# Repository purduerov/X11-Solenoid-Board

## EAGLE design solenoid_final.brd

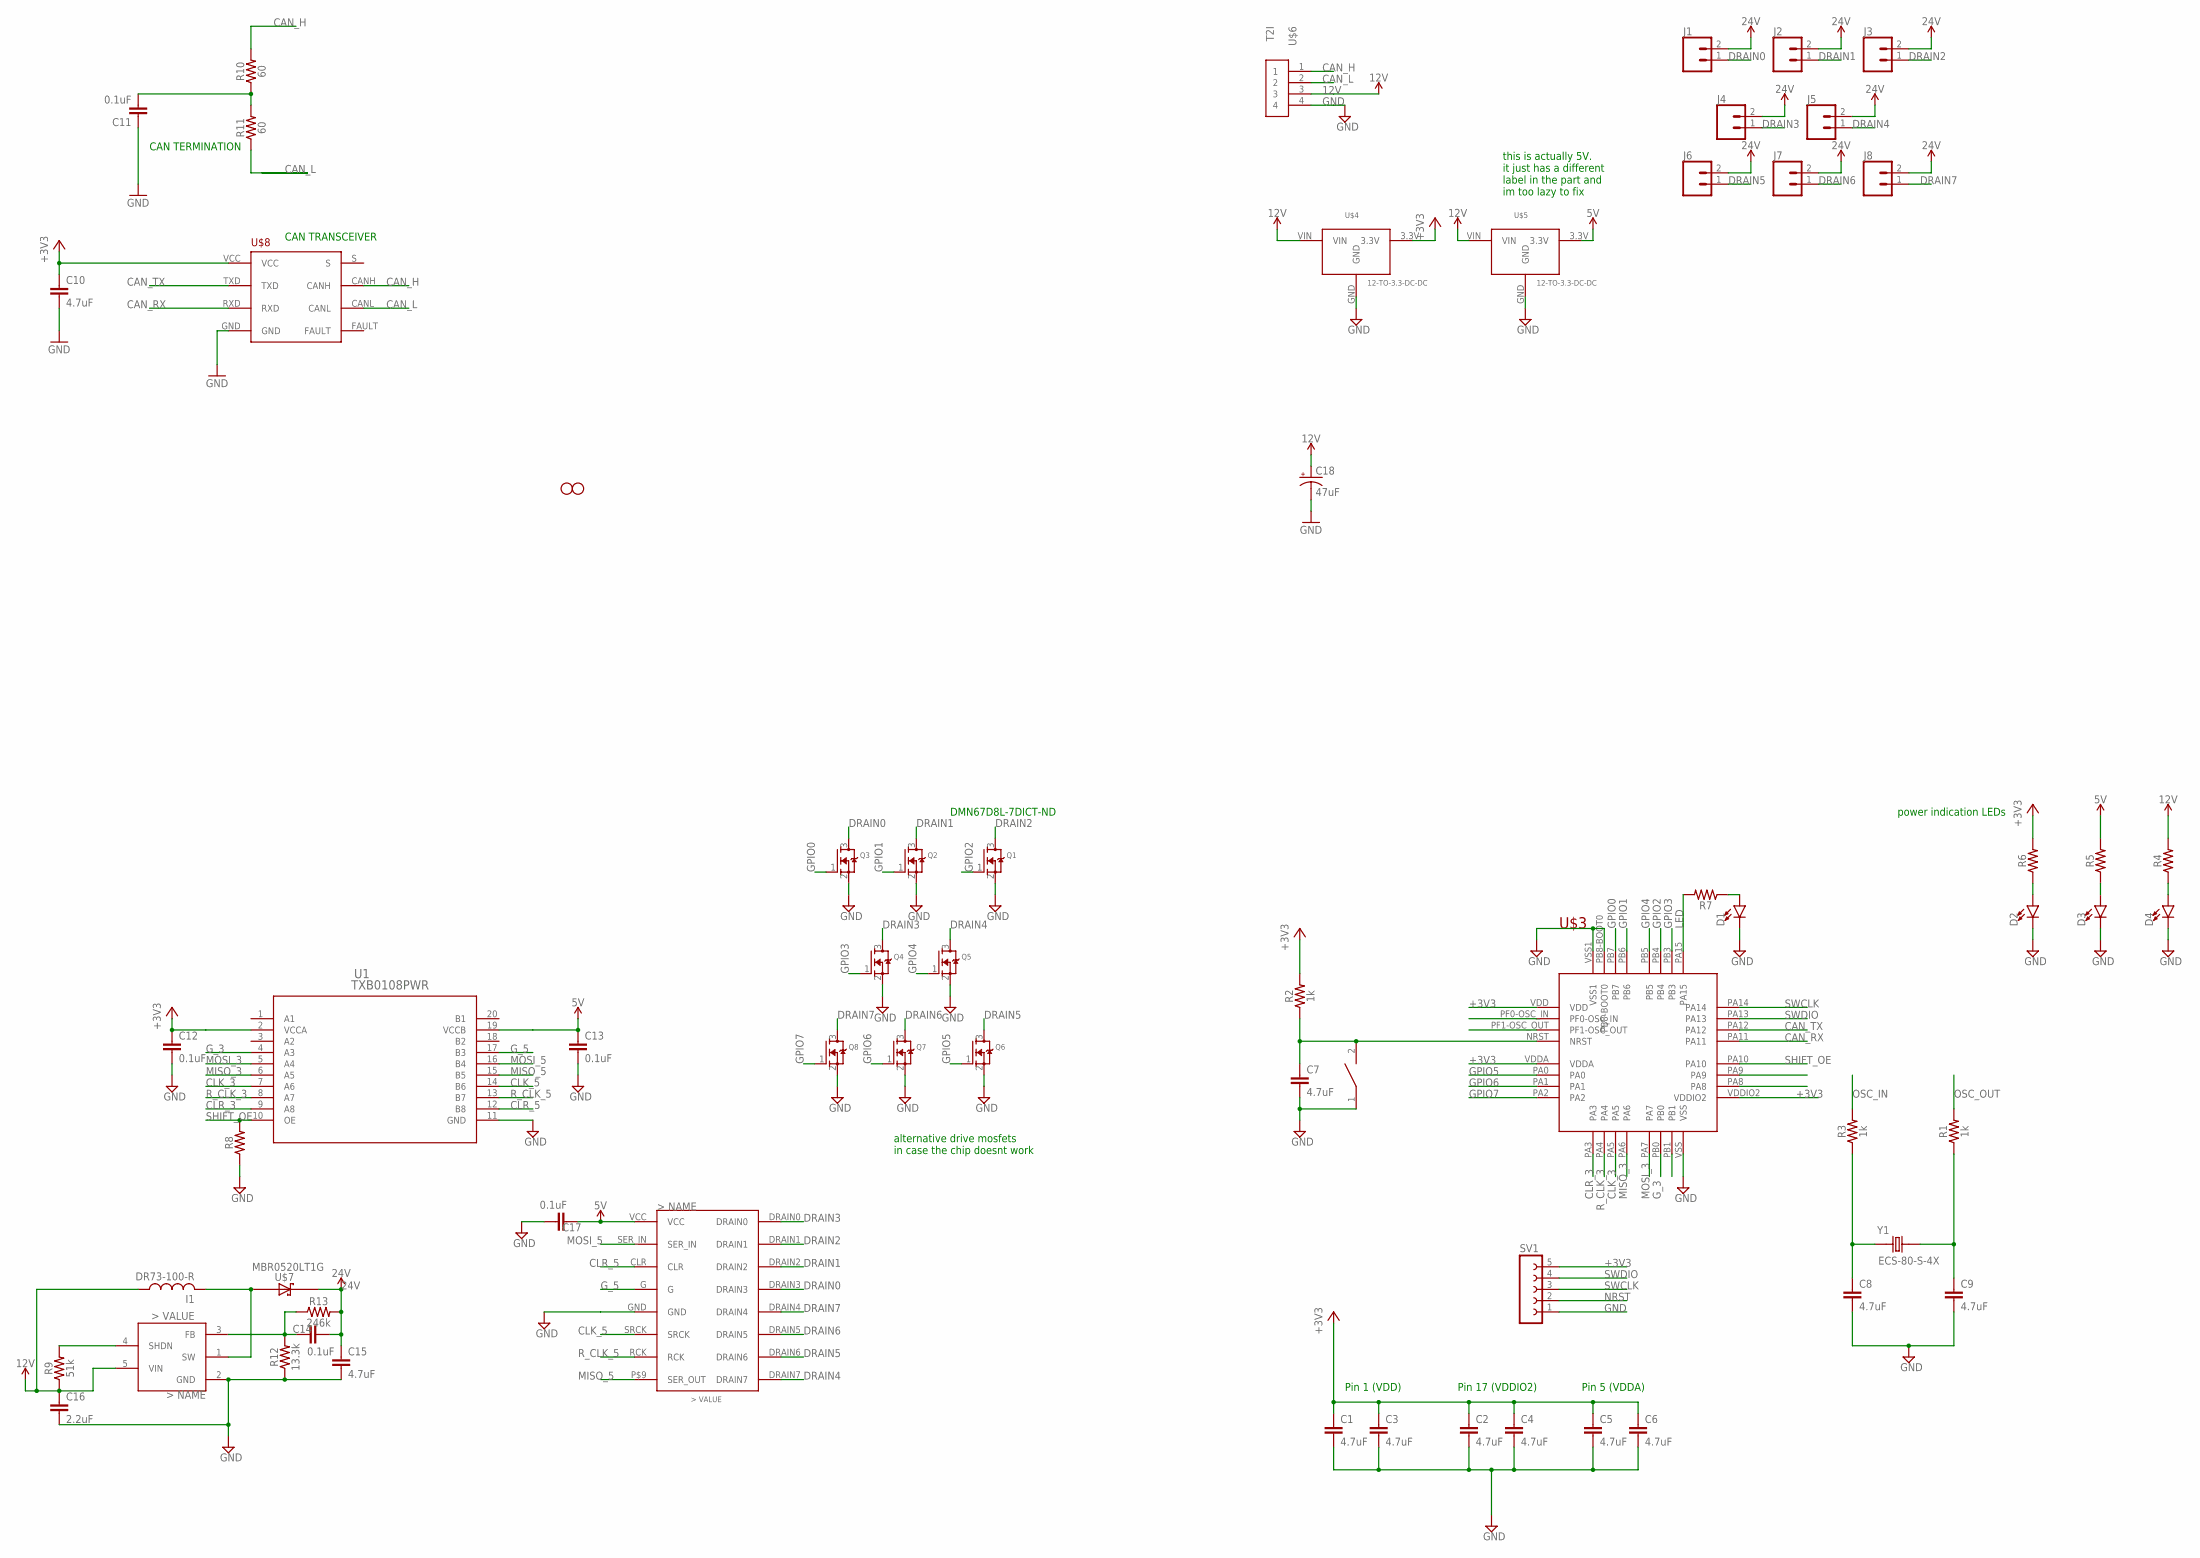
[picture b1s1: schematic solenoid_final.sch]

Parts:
C1, C2, C3, C4, C5, C6, C7, C8, C9, C10, C15: 4.7uF; 0603
C11, C12, C13, C14, C17: 0.1uF; 0603
C16: 2.2uF; 0603
C18: 47uF; PANASONIC_D
D1, D2, D3, D4: LED0603; LED-0603
H1, H2: STAND-OFF
I1: DR73-100-R
J1, J2, J3, J4, J5, J6, J7, J8: CONN_02; 1X02
Q1, Q2, Q3, Q4, Q5, Q6, Q7, Q8: MOSFET-NWIDE; SOT23-WIDE
R1, R2, R3: 1k; 0603
R4, R5, R6, R7, R8: 0603
R9: 51k; 0603
R10, R11: 60; 0603
R12: 13.3k; 0603
R13: 246k; 0603
RESET: SWITCH; SW_2512
SV1: FE05-1
U1: TXB0108PWR; PW20
U$1: SHIFT_REGISTER
U$2: LM27313; SOT95P300X145-5
U$3: STM32F042K6T6
U$4, U$5: 12-TO-3.3-DC-DC; MURATA-DCDC
U$6: T2I
U$7: MBR0520LT1G; SOD3716X135
U$8: TCAN337D
Y1: ECS-80-S-4X; XTAL_ECS-80-S-4X

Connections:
5V: C13.1, C17.1, R5.2, U1.19 (VCCB), U$1.VCC, U$5.3.3V
12V: C16.1, C18.+, I1.1, R4.2, R9.1, U$2.5 (VIN), U$4.VIN, U$5.VIN, U$6.3
24V: C14.2, C15.1, J1.2, J2.2, J3.2, J4.2, J5.2, J6.2, J7.2, J8.2, R13.2, U$7.2 (C)
+3V3: C1.1, C2.1, C3.1, C4.1, C5.1, C6.1, C10.1, C12.1, R2.2, R6.2, SV1.5, U1.2 (VCCA), U$3.VDD, U$3.VDDA, U$3.VDDIO2, U$4.3.3V, U$8.VCC
CAN_H: R10.2, U$6.1, U$8.CANH
CAN_L: R11.1, U$6.2, U$8.CANL
CAN_RX: U$3.PA11, U$8.RXD
CAN_TX: U$3.PA12, U$8.TXD
CLK_3: U1.7 (A6), U$3.PA5
CLK_5: U1.14 (B6), U$1.SRCK
CLR_3: U1.9 (A8), U$3.PA3
CLR_5: U1.12 (B8), U$1.CLR
DRAIN0: J1.1, Q3.3 (D), U$1.DRAIN3
DRAIN1: J2.1, Q2.3 (D), U$1.DRAIN2
DRAIN2: J3.1, Q1.3 (D), U$1.DRAIN1
DRAIN3: J4.1, Q4.3 (D), U$1.DRAIN0
DRAIN4: J5.1, Q5.3 (D), U$1.DRAIN7
DRAIN5: J6.1, Q6.3 (D), U$1.DRAIN6
DRAIN6: J7.1, Q7.3 (D), U$1.DRAIN5
DRAIN7: J8.1, Q8.3 (D), U$1.DRAIN4
GND: C1.2, C2.2, C3.2, C4.2, C5.2, C6.2, C7.2, C8.2, C9.2, C10.2, C11.1, C12.2, C13.2, C15.2, C16.2, C17.2, C18.-, D1.C, D2.C, D3.C, D4.C, Q1.2 (S), Q2.2 (S), Q3.2 (S), Q4.2 (S), Q5.2 (S), Q6.2 (S), Q7.2 (S), Q8.2 (S), R8.1, R12.1, RESET.1, SV1.1, U1.11 (GND), U$1.GND, U$2.2 (GND), U$3.PB8-BOOT0, U$3.VSS, U$3.VSS1, U$4.GND, U$5.GND, U$6.4, U$8.GND
GPIO0: Q3.1 (G), U$3.PB7
GPIO1: Q2.1 (G), U$3.PB6
GPIO2: Q1.1 (G), U$3.PB4
GPIO3: Q4.1 (G), U$3.PB3
GPIO4: Q5.1 (G), U$3.PB5
GPIO5: Q6.1 (G), U$3.PA0
GPIO6: Q7.1 (G), U$3.PA1
GPIO7: Q8.1 (G), U$3.PA2
G_3: U1.4 (A3), U$3.PB0
G_5: U1.17 (B3), U$1.G
LED: R7.2, U$3.PA15
MISO_3: U1.6 (A5), U$3.PA6
MISO_5: U1.15 (B5), U$1.P$9 (SER_OUT)
MOSI_3: U1.5 (A4), U$3.PA7
MOSI_5: U1.16 (B4), U$1.SER_IN
unnamed: C9.1, R1.1, Y1.2
unnamed: C8.1, R3.1, Y1.1
unnamed: R9.2, U$2.4 (SHDN)
unnamed: C11.2, R10.1, R11.2
unnamed: I1.2, U$2.1 (SW), U$7.1 (A)
unnamed: C14.1, R12.2, R13.1, U$2.3 (FB)
unnamed: D1.A, R7.1
unnamed: D4.A, R4.1
unnamed: D3.A, R5.1
unnamed: D2.A, R6.1
NRST: C7.1, R2.1, RESET.2, SV1.2, U$3.NRST
OSC_IN: R3.2, U$3.PF0-OSC_IN
OSC_OUT: R1.2, U$3.PF1-OSC_OUT
R_CLK_3: U1.8 (A7), U$3.PA4
R_CLK_5: U1.13 (B7), U$1.RCK
SHIFT_OE: R8.2, U1.10 (OE), U$3.PA10
SWCLK: SV1.3, U$3.PA14
SWDIO: SV1.4, U$3.PA13

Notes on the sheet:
Pin 1 (VDD)
Pin 17 (VDDIO2)
Pin 5 (VDDA)
CAN TRANSCEIVER
CAN TERMINATION
this is actually 5V. it just has a different label in the part and im too lazy to fix
DMN67D8L-7DICT-ND
power indication LEDs
alternative drive mosfets in case the chip doesnt work

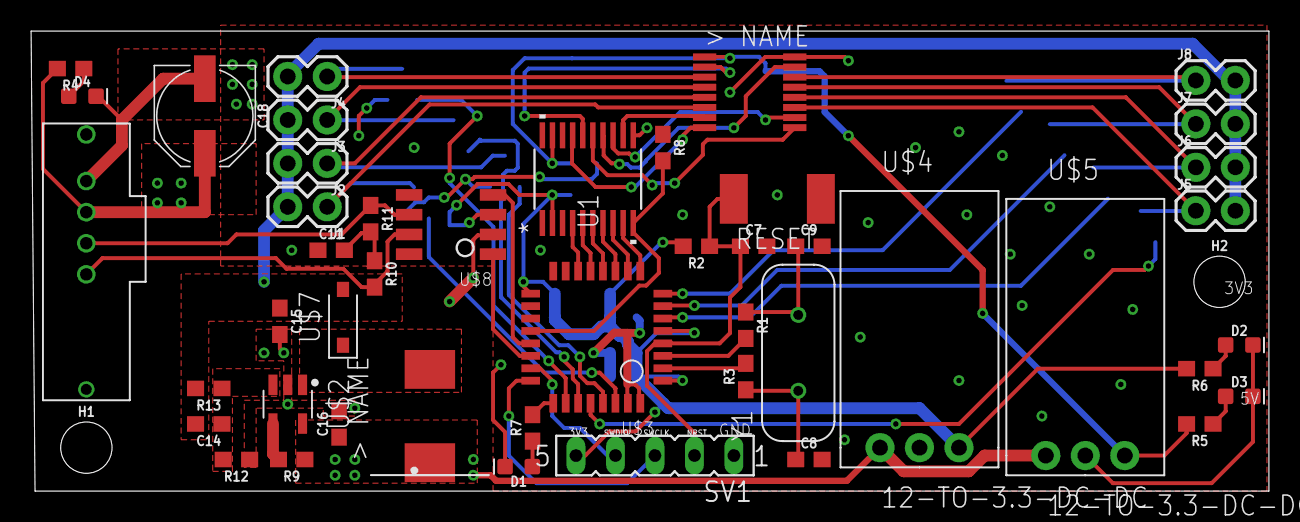
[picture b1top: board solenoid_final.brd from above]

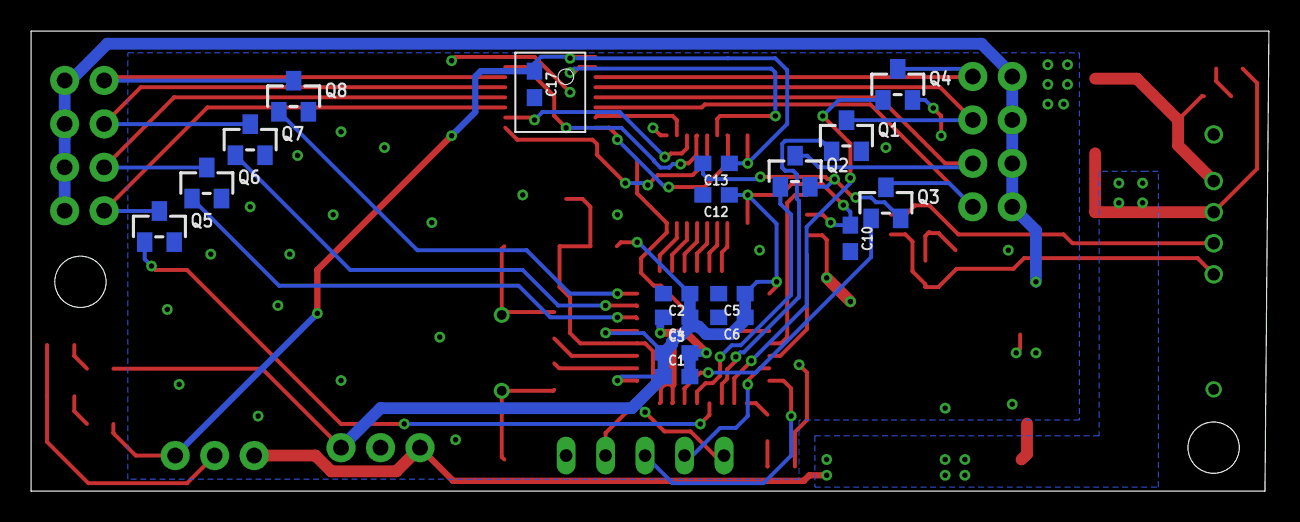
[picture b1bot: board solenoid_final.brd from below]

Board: 2 copper layers, 79.6 x 29.6 mm, 66 parts (18 on the bottom side), 54 nets.

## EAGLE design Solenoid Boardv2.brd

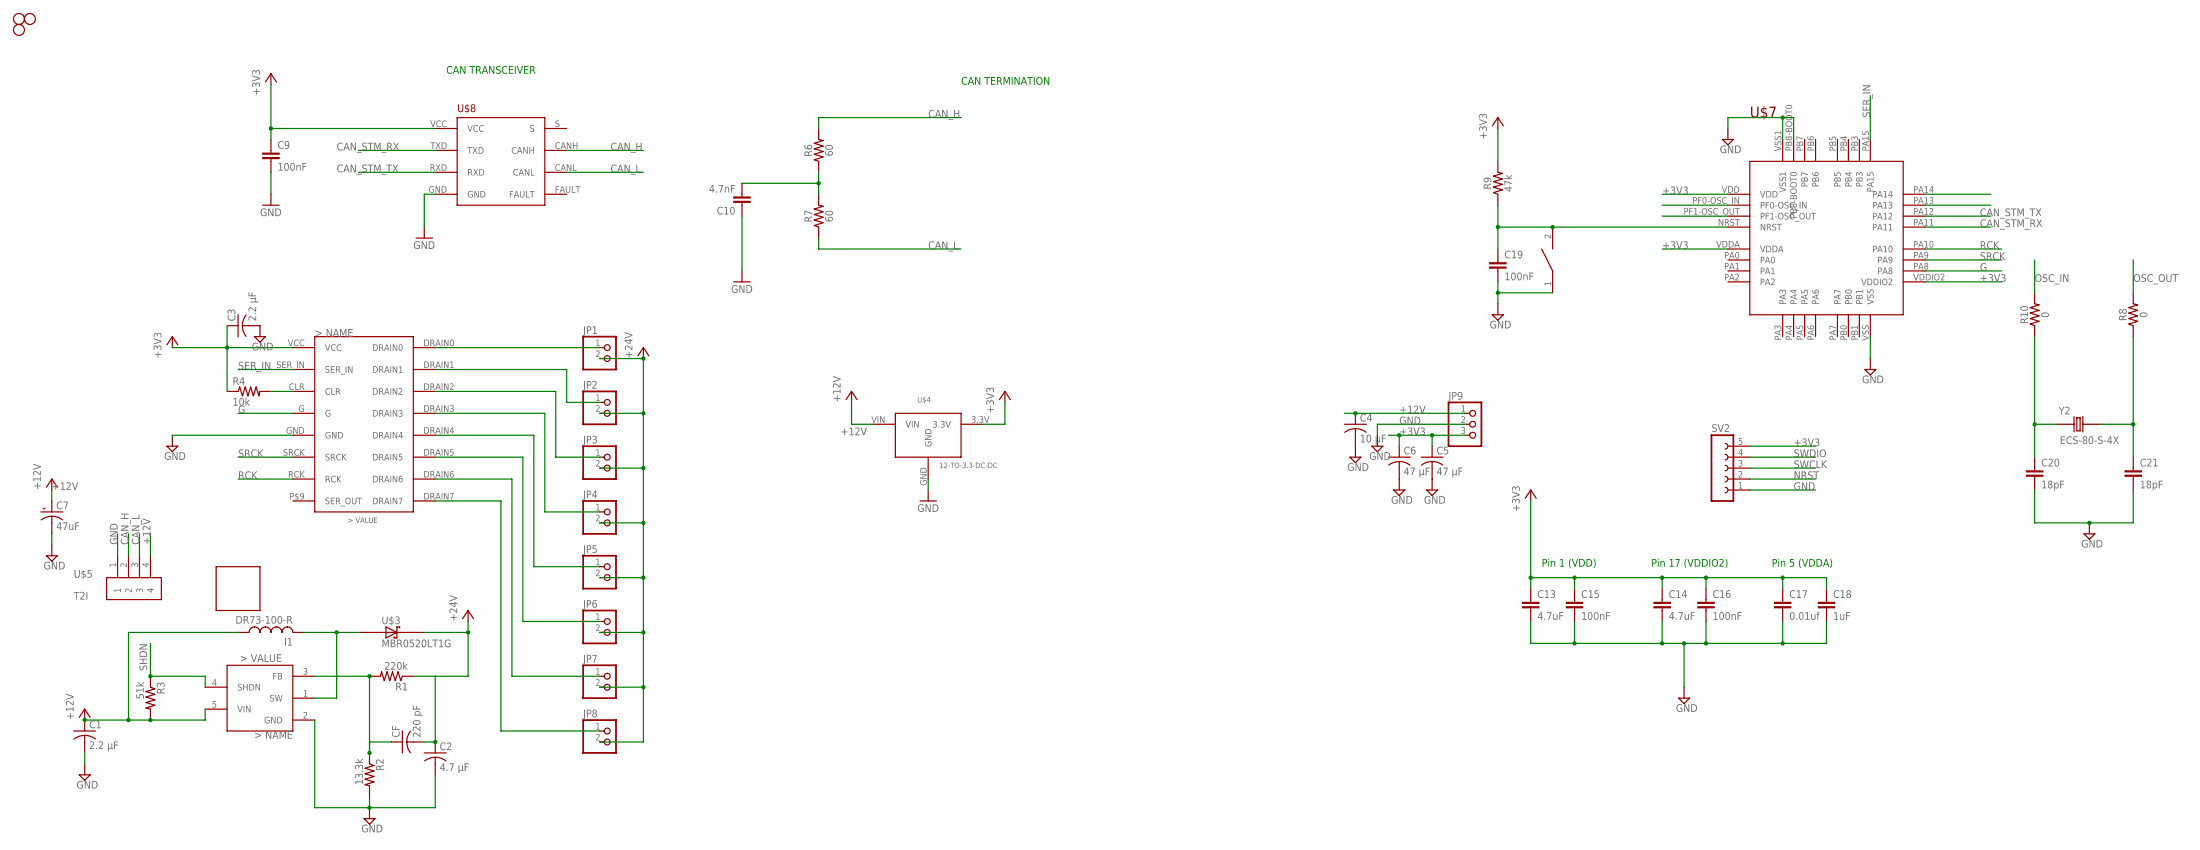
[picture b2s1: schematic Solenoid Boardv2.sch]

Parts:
C1, C3: 2.2 µF; C0805
C2: 4.7 µF; C0805
C4: 10 µF; C0805
C5, C6: 47 µF; C0805
C7: 47uF; PANASONIC_D
C9, C15, C16, C19: 100nF; 0603
C10: 4.7nF; 0603
C13, C14: 4.7uF; 0603
C17: 0.01uf; 0603
C18: 1uF; 0603
C20, C21: 18pF; 0603
CF: 220 pF; C0805
H1, H2, H3: STAND-OFF
I1: DR73-100-R
JP1, JP2, JP3, JP4, JP5, JP6, JP7, JP8: PINHD-1X2; 1X02
JP9: PINHD-1X3; 1X03
R1: 220k; R0603
R2: 13.3k; R0603
R3: 51k; R0603
R4: 10k; R0603
R6, R7: 60; 0603
R8, R10: 0; 0603
R9: 47k; 0603
RESET1: SWITCH; SW_2512
SV2: FE05-1
U$1: SHIFT_REGISTER
U$2: LM27313; SOT95P300X145-5
U$3: MBR0520LT1G; SOD3716X135
U$4: 12-TO-3.3-DC-DC; MURATA-DCDC
U$5: T2I
U$6: BOARDPNE; PNE
U$7: STM32F042K6T6
U$8: TCAN337D
Y2: ECS-80-S-4X; XTAL_ECS-80-S-4X

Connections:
+3V3: C3.1, C5.1, C6.1, C9.1, C13.1, C14.1, C15.1, C16.1, C17.1, C18.1, JP9.3, R4.1, R9.2, SV2.5, U$1.VCC, U$4.3.3V, U$7.VDD, U$7.VDDA, U$7.VDDIO2, U$8.VCC
+12V: C1.1, C4.1, C7.+, I1.1, JP9.1, R3.2, U$2.5 (VIN), U$4.VIN, U$5.4
+24V: C2.1, CF.2, JP1.2, JP2.2, JP3.2, JP4.2, JP5.2, JP6.2, JP7.2, JP8.2, R1.1, U$3.2 (C)
CAN_H: R6.2, U$5.2, U$8.CANH
CAN_L: R7.1, U$5.3, U$8.CANL
CAN_STM_RX: U$7.PA11, U$8.TXD
CAN_STM_TX: U$7.PA12, U$8.RXD
CLR: R4.2, U$1.CLR
DRAIN0: JP1.1, U$1.DRAIN0
DRAIN1: JP2.1, U$1.DRAIN1
DRAIN2: JP3.1, U$1.DRAIN2
DRAIN3: JP4.1, U$1.DRAIN3
DRAIN4: JP5.1, U$1.DRAIN4
DRAIN5: JP6.1, U$1.DRAIN5
DRAIN6: JP7.1, U$1.DRAIN6
DRAIN7: JP8.1, U$1.DRAIN7
FB: CF.1, R1.2, R2.1, U$2.3 (FB)
G: U$1.G, U$7.PA8
GND: C1.2, C2.2, C3.2, C4.2, C5.2, C6.2, C7.-, C9.2, C10.1, C13.2, C14.2, C15.2, C16.2, C17.2, C18.2, C19.2, C20.2, C21.2, JP9.2, R2.2, RESET1.1, SV2.1, U$1.GND, U$2.2 (GND), U$4.GND, U$5.1, U$7.PB8-BOOT0, U$7.VSS, U$7.VSS1, U$8.GND
unnamed: C21.1, R8.1, Y2.2
unnamed: C20.1, R10.1, Y2.1
unnamed: C10.2, R6.1, R7.2
NRST: C19.1, R9.1, RESET1.2, SV2.2, U$7.NRST
OSC_IN: R10.2, U$7.PF0-OSC_IN
OSC_OUT: R8.2, U$7.PF1-OSC_OUT
RCK: U$1.RCK, U$7.PA10
SER_IN: U$1.SER_IN, U$7.PA15
SHDN: R3.1, U$2.4 (SHDN)
SRCK: U$1.SRCK, U$7.PA9
SW: I1.2, U$2.1 (SW), U$3.1 (A)
SWCLK: SV2.3, U$7.PA14
SWDIO: SV2.4, U$7.PA13

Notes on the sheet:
Pin 1 (VDD)
Pin 17 (VDDIO2)
Pin 5 (VDDA)
CAN TRANSCEIVER
CAN TERMINATION

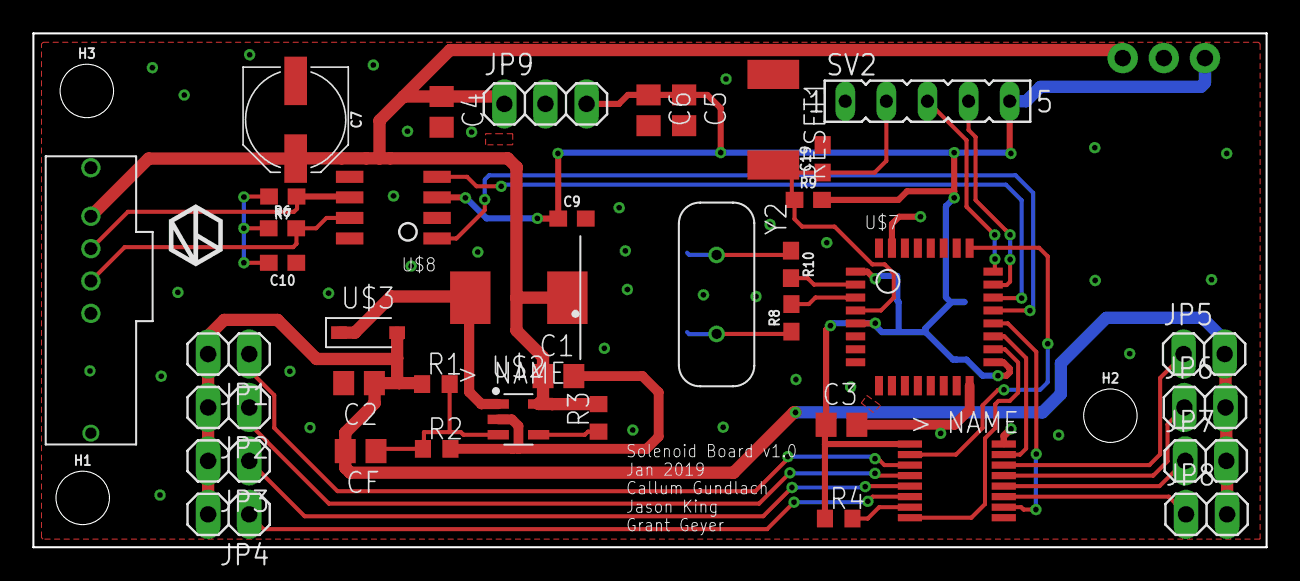
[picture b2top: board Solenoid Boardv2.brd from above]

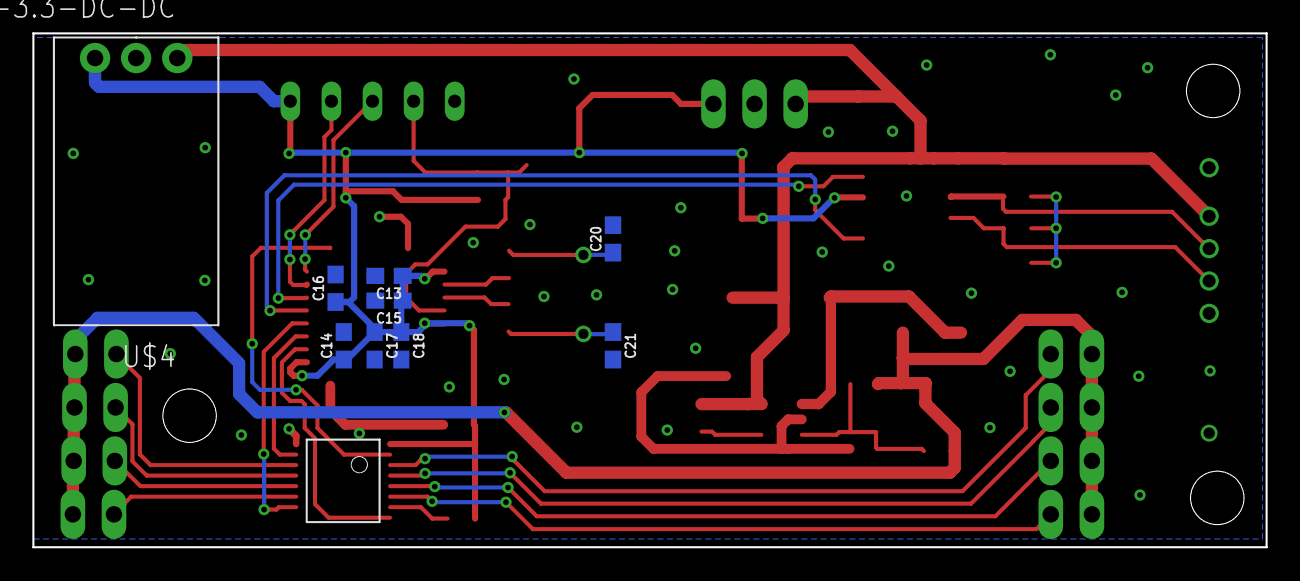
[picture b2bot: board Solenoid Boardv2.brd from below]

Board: 2 copper layers, 76.2 x 31.8 mm, 52 parts (9 on the bottom side), 32 nets.

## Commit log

2018-10-20 Created board schematic (blank)
2018-10-20 Copied .gitignore
2018-11-08 Added frame and stm block
2018-11-10 Created the board layout
2018-11-15 Routed most of the board
2018-11-29 Well it's trash but board layout v1 is done
2018-11-29 Started work on the solenoid board v2
2018-12-02 Made progress on V2, added polygons and headers for step down converter
2019-01-03 Added the can module
2019-01-04 changes from design review
2019-01-05 WIP changing route widths
2019-01-05 Added required revisions from design review
2019-01-05 Moved nsrt around the osc signals
2019-01-05 Fixed the via stitching
2019-01-06 Fixed airwires and aligned the solenoid header pins
2019-01-06 Grant's revisions. Detailed in notes.txt
2019-01-06 Added question add ground plane and inductor
2019-01-07 Fixed some clearance issues
2019-01-07 fixed a weird trace, moved a standoff hole a little so that it didnt overlap with a trace
2019-01-07 GND wasnt fully routed, fixed
2019-03-25 revised boost converter resistors and added data sheet for boost converter
2019-04-09 Some changes that existed
2019-04-09 Added real version

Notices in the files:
parts and their libraries:
SparkFun-Capacitors: Licensing: Creative Commons ShareAlike 4.0 International - https://creativecommons.org/licenses/by-sa/4.0
microbuilder: This work is placed in the public domain, and may be freely used for commercial and non-commercial work with the following conditions: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
